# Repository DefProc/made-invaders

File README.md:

# made-invaders

A repo and issues list for the Made Invaders installation

The original test target display is the [ledframe](https://git.defproc.co.uk/DefProc/ledframe)

larger issues and discussins are in the [issues](https://github.com/DoESLiverpool/made-invaders/issues) but minute-by-minute planning is in the [trello board](https://trello.com/b/ncKjq608/made-invaders)

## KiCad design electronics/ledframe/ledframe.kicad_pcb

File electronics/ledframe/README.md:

Known Issues
============

rev 1
-----

 * The 5V and ground on CON1 are reversed
   * **The D1, U1 and U3 WILL be damaged if the board is powered up**
   * Cutting the ground connections and the 5V line around the pads *must* be done
   before soldering. Then reversed connections will need to be added manually.
 * both SW1 and SW2 are rotated 90 degress from the correct connections.
   * Cutting diagonally opposed legs from the button before assembly will allow
   normal operation.
 * The ISCP slave select (SS) line is shared between IC1 and U2.
   * The ATmega *must* be programmed with a bootloader *before* soldering.
   * To program via ISCP, cut the RADIO_SS line between IC1 and U2.
 * The level converter (Q2, R3, R4) is too slow for the transmission speed required
 for the WS2812b LEDs.
   * Do not place Q1, R3 or R4. Make a bridge connection between pins 2–3 of Q2.

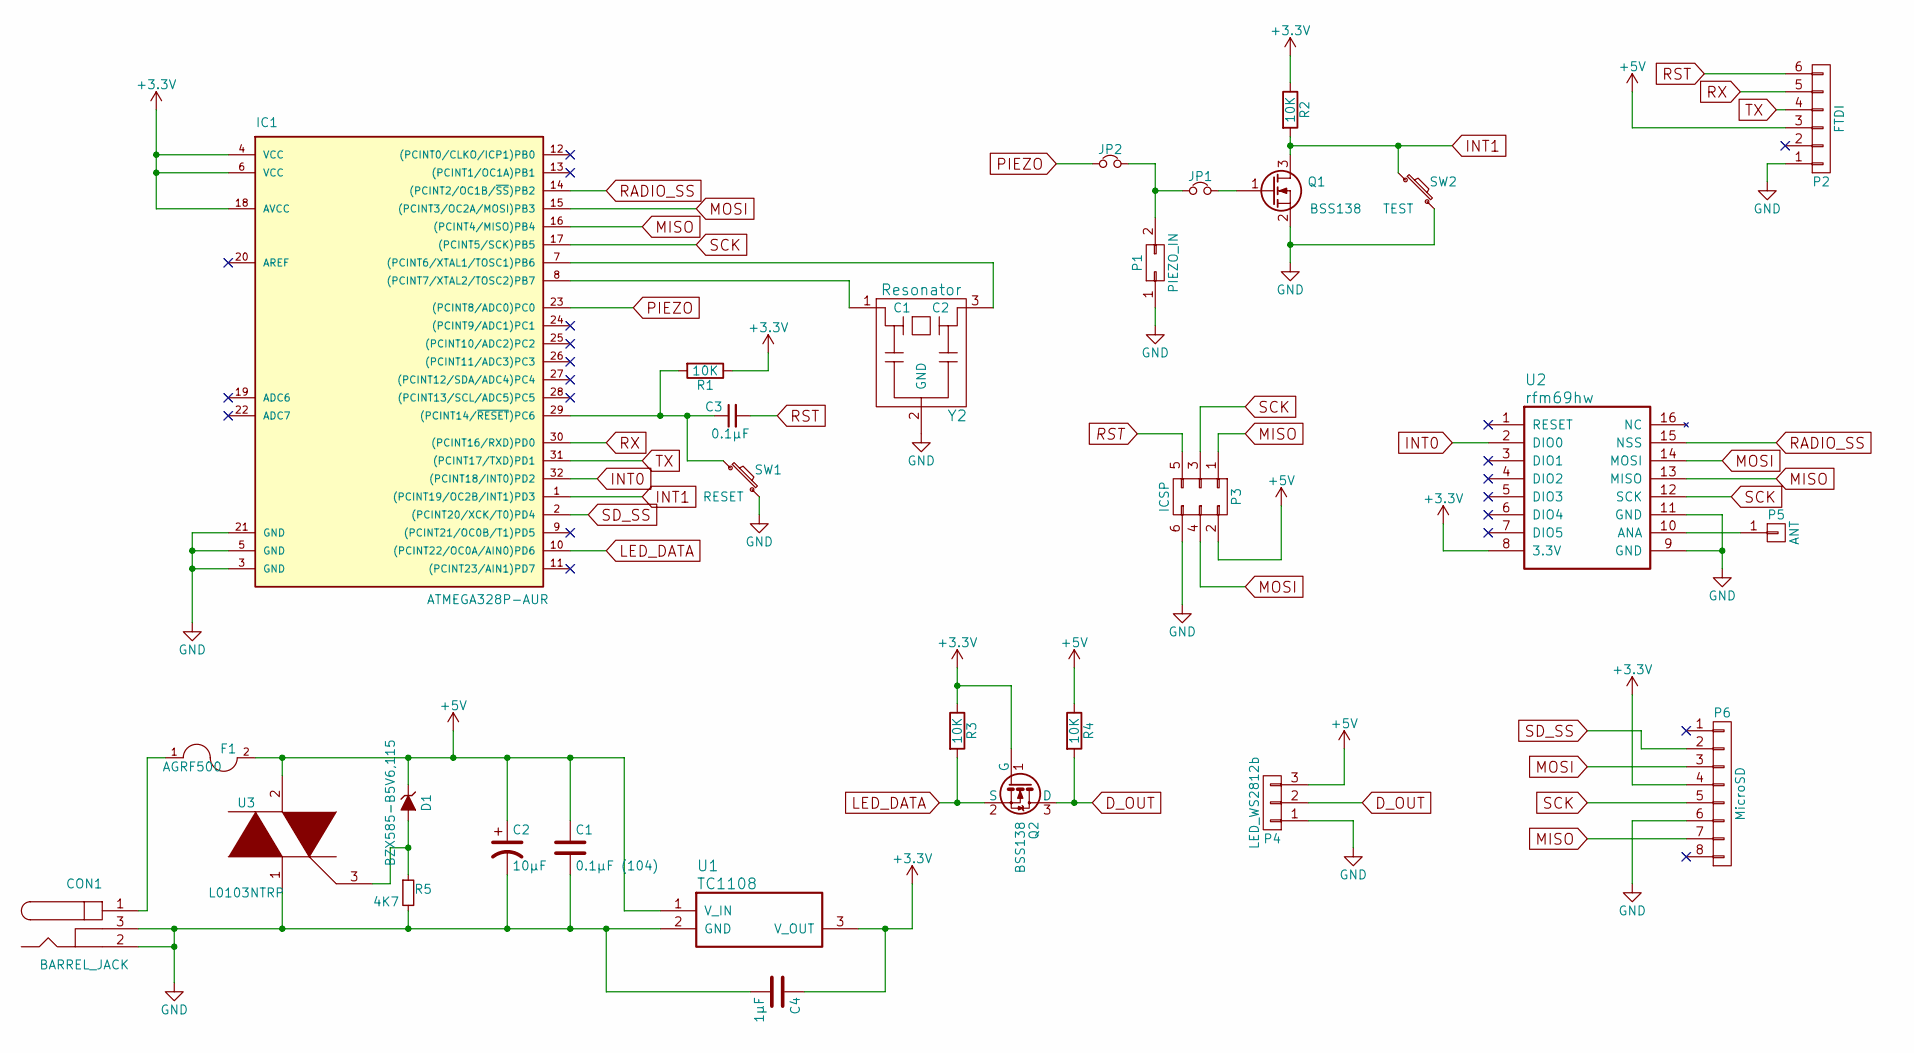
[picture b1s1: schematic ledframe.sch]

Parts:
C1: 0.1µF (104); C_0603
C2: 10µF; c_elec_3x5.3
C3: 0.1µF; C_0603
C4: 1µF; C_0805
CON1: BARREL_JACK
D1: BZX585-B5V6,115; SOD-523
F1: AGRF500; Resistor_Horizontal_RM7mm
IC1: ATMEGA328P-AUR; TQFP-32_7x7mm_Pitch0.8mm
JP1, JP2: Jumper_NC_Small; NC_SMD_JPR
P1: PIEZO_IN; Pin_Header_Straight_2x01
P2: FTDI; Pin_Header_Straight_1x06
P3: ICSP; Pin_Header_Straight_2x03
P4: LED_WS2812b; Pin_Header_Straight_1x03
P5: ANT; Socket_Strip_Straight_1x01
P6: MicroSD; MicroSD_Molex_47309
Q1, Q2: BSS138; SOT-23
R1, R2, R3, R4: 10K; R_0603
R5: 4K7; R_0603
SW1: RESET; KSEx00G_SW
SW2: TEST; KSEx00G_SW
U1: TC1108; SOT-223
U2: rfm69hw; DIP-16_W7.62mm
U3: L0103NTRP; SOT-223
Y2: Resonator; Resonator_3.2x1.3

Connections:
+3V3: C4.1, IC1.4 (VCC), IC1.6 (VCC), IC1.18 (AVCC), P6.4, Q2.1 (G), R1.1, R2.1, R3.1, U1.3 (V_OUT), U2.8 (3.3V)
+5V: C1.1, C2.1, D1.1 (K), F1.2, P2.3, P3.2, P4.3, R4.1, U1.1 (V_IN), U3.2
D_OUT: P4.2, Q2.3 (D), R4.2
GND: C1.2, C2.2, C4.2, CON1.2, CON1.3, IC1.3 (GND), IC1.5 (GND), IC1.21 (GND), P1.1, P2.1, P3.6, P4.1, P6.6, Q1.2 (S), R5.2, SW1.2, SW2.2, U1.2 (GND), U2.9 (GND), U2.11 (GND), U3.1, Y2.2 (GND)
INT0: IC1.32 ((PCINT18/INT0)PD2), U2.2 (DIO0)
INT1: IC1.1 ((PCINT19/OC2B/INT1)PD3), Q1.3 (D), R2.2, SW2.1
LED_DATA: IC1.10 ((PCINT22/OC0A/AIN0)PD6), Q2.2 (S), R3.2
MISO: IC1.16 ((PCINT4/MISO)PB4), P3.1, P6.7, U2.13 (MISO)
MOSI: IC1.15 ((PCINT3/OC2A/MOSI)PB3), P3.4, P6.3, U2.14 (MOSI)
unnamed: C3.1, IC1.29 ((PCINT14/~RESET~)PC6), R1.2, SW1.1
unnamed: CON1.1, F1.1
unnamed: D1.2 (A), R5.1, U3.3
unnamed: IC1.7 ((PCINT6/XTAL1/TOSC1)PB6), Y2.3 (C2)
unnamed: IC1.8 ((PCINT7/XTAL2/TOSC2)PB7), Y2.1 (C1)
unnamed: JP1.1, JP2.2, P1.2
unnamed: JP1.2, Q1.1 (G)
unnamed: P5.1, U2.10 (ANA)
PIEZO: IC1.23 ((PCINT8/ADC0)PC0), JP2.1
RADIO_SS: IC1.14 ((PCINT2/OC1B/~SS~)PB2), U2.15 (NSS)
RST: C3.2, P2.6, P3.5
RX: IC1.30 ((PCINT16/RXD)PD0), P2.5
SCK: IC1.17 ((PCINT5/SCK)PB5), P3.3, P6.5, U2.12 (SCK)
SD_SS: IC1.2 ((PCINT20/XCK/T0)PD4), P6.2
TX: IC1.31 ((PCINT17/TXD)PD1), P2.4

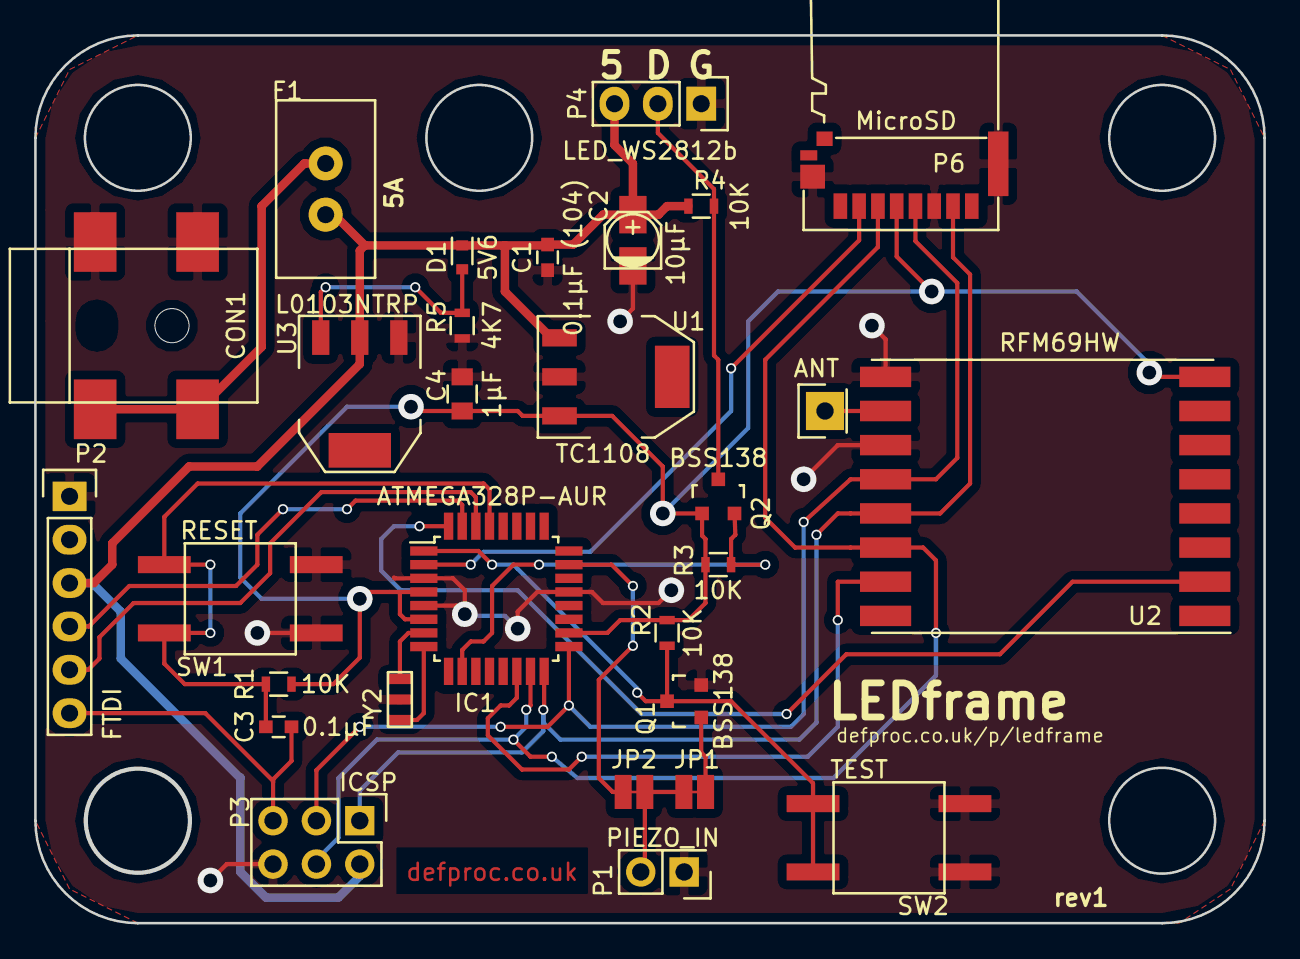
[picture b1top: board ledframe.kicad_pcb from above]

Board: 2 copper layers, 72.0 x 52.0 mm, 29 parts (0 on the bottom side), 24 nets.

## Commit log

2016-03-02 include ledframe link
2016-03-02 draft of target circuit
2016-03-14 EOD: there's a circuit, but no board layout yet
2016-03-18 included the inital test images for the ledframe
2016-03-18 Made an Minecraft mcdirtblock.bmp
2016-03-27 changed to resonator
2016-03-27 draft layout. still needs rfm69 and resonator footprints
2016-03-27 first draft routing
2016-03-27 included the missing resonator(!)
2016-03-28 issues and trello board links
2016-03-29 generated gerbers
2016-03-29 removed an alignment target from the board
2016-03-29 included a link to the bom
2016-04-02 first draft of the target boxes (at 0.1.1)
2016-04-03 removed the text and elastics holes; added a space for the piezo to go through
2016-04-07 brought across the MFUKLC arduino code
2016-04-07 included a slot for the piezo to go through
2016-04-07 included SDFat, RFM69 and FastLED libraries
2016-04-07 registration station code moved over from mfuklc
2016-04-07 new string test for checking LEDs before making the arrays
2016-04-08 read out the invader.bmp file so we can stick it in memory later
2016-04-08 and try holding the invader.bmp as a const
2016-04-08 EOD: created a "change on piezo" sketch
2016-04-11 fixed the nerf_test, and included TimerOne library too
2016-04-11 draft logo
2016-04-13 main play stand cut files
2016-04-13 and a cut file for the rfid area cover
2016-04-14 cut files for the power supply cover
2016-04-14 change to sdcard invader logo, and have 9×9 array in 90 led string
2016-04-14 added the known issues with the rev1 ledframe boards
2016-04-16 included the vinyl cut files for the box pixel patterns
2016-04-16 included the interrupt pin on the sensor too
2016-04-16 radio send and receive test with RFM69s
2016-04-16 included some comments on broadcast sending and promiscuous listening
2016-04-17 moved to common constants and secrets files
2016-04-17 added new GET_READY command
2016-04-17 the start of the draft target_node code, with scrolling or stacked animation support
2016-04-17 EOD: some tidying up, and added start time variable to the target_node
2016-04-19 pin4 for SD SS
2016-04-19 include the SPIflash and WirelessProgramming libraries
2016-04-19 included wireless programming option for the test_receiver
2016-04-19 reversed the radio send order till after the image change
2016-04-19 added the required libs, and drafted a main controller sketch
2016-04-19 draft of the other play modes for the targets
2016-04-19 lets at least stick to the common baud rate(!)
2016-04-19 draft of the RFM69 to RPi translator
2016-04-19 and the typos fixed…
2016-04-20 draft of the RFM69 activated timer (and scoreboard) code
2016-04-20 changed the get ready time to 30000
2016-04-20 some adjustments to the main controller for debugging and play flow
2016-04-20 include the rfid module user guide
2016-04-20 corrected the registration station, and added the get ready message
2016-04-20 better logging, more broadcasts, actually made the take_photo request
2016-04-20 just prefill the rfid number with zeros
2016-04-20 reduced the baud rate on reg_stn down to 9600 for reliability
2016-04-20 and sorted the rfid reader (n.b. must call Wire.begin() for I2C!
2016-04-20 added twitter banner formatted png
2016-04-20 more robust start/cancel button, broadcast start game later
2016-04-20 new READY mode and operational tweaks
2016-04-20 corrected the timer, set the main controller timer flow and added more images to the target
2016-04-20 and the timers must be unsigned longs!!
2016-04-20 added the Entropy library to seed different patterns to each target
2016-04-20 added node setting by serial, and stored on EEPROM
2016-04-20 generated a set of static images
2016-04-21 added music codec tests to the main controller
2016-04-21 included options for timer OR scoreboard
2016-04-21 added the startup sounds
2016-04-21 updated pin defs, so mp3 player DREQ is on INT0
2016-04-21 Music Files
    In game music
2016-04-21 Moved the @epsaul sounds into platformio/main_controller/src
2016-04-21 Added new sound file calls where it looked like they should go with comments, needs checking! Also moved the actual files around
2016-04-21 Removed old mp3 files
2016-04-21 Removed copies of files with wrong names
2016-04-21 Added sounds again before realising they dont need to be here
2016-04-21 Put the sound files somewhere sensible, need to include the marioPip and countdown sounds later
2016-04-21 explode animation, fast change, and read SD for file numbers
2016-04-21 Added the original mario countdown mp3s
2016-04-21 Fixed file names typos and changed mp3 file permissions
2016-04-21 removed acks in promiscuous
2016-04-21 made sure we're not sending ack requests with the broadcast message
2016-04-21 removed acks and changed to normal moteino
2016-04-21 slowed down the SD card, stopped any idle animations
2016-04-22 Changed the random function to choose between the LEVEL.mp3 char array index. Hope that works
2016-04-22 OTD: sd.begin on failed image, reduced serial on bmpDraw()
2016-04-22 more images
2016-04-23 OTD: timings and start sounds
2016-04-23 lets just stash this stuff I've broken
2016-04-23 added target error reporting on the leds, and red flash on END_GAME
2016-04-23 actually stored scores as longs to add up(!) and more exciting scores
2016-05-27 moved sounds to numbered files/folders for SOMO-II use
2016-06-20 Normalised all to -2dB, removed any DC offset in Audacity
2016-06-21 EOD: somo-ii sound working, countdown running to time
2016-06-21 EOD: sorted the countdown on the main controller, draft of the scoreboard 5 second countdown
2016-06-21 changed the idle music timing to 3min on, 3min off
2016-06-22 synced the countdowntimer and sound
2016-06-22 added an image testing mode
2016-06-23 image check now runs when counting the files
2016-06-23 bug fixes and smooth running on the main and targets
2016-06-23 revised the startup to say v1.1 on the target_node sketch
2016-06-23 should show zero from GET_READY signal
2016-06-23 put tested ACK before processing
2016-06-23 secret
2016-06-24 removed promiscuous mode to quiet the incoming traffic
2016-10-25 dummy main controller sketch
2016-10-26 lots more comments
2016-10-26 added autoplay mode (30s play, 60s wait)
2016-10-27 corrected auto start and added the countdown timer radio calls
2017-03-28 added a 0.1 second delay for each sucessive target on startup
2017-04-04 added pack list
2017-07-24 Checked Pack list
